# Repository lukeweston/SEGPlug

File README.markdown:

**SEGPlug: A single-channel, single-phase, portable, wireless mesh-networked smart energy data acquisition and control appliance**

Design by Luke Weston, 2011-2012
(c) Luke Weston 2011-2012

This hardware design is released to you under the CERN Open Hardware License: http://ohwr.org/cernohl

The Smart Energy Groups SEGPlug is a small, visually unintrusive and portable device which plugs in to a domestic mains power outlet or cable and plugs into a mains-powered
load device. It is (with a small hardware reconfiguration) compatible with worldwide mains power grids, at 110-240VAC and 50-60 Hz. This "Internet of Things" device collects
data from its sensors and data acquisition circuits and transmits this data to a distributed network and ultimately to the Internet and receives commands from a distributed
network and/or the Internet and responds to such commands, for example by switching its onboard power relay on or off. 

SEGPlug acquires the voltage waveform across the load device(s) and the current waveform being consumed by the load device(s) and calculates instantaneous power draw as well
as energy consumption integrated across some period of time, and complex AC power characteristics such as phase angle, reactive power and power factor.

SEGPlug also incorporates a relay allowing the power supply to the load device to be completely switched off and switched on at the command of the device's (very low power)
internal microcontroller.

SEGPlug is powered from the mains power supply which it is plugged into - no additional power supplies or cables are required, everything is integrated into one clean and
simple plug-in cable.

SEGPlug sends and receives data and commands over a wireless radio mesh network, back to a gateway device which bridges the wireless mesh network onto an existing local area
network which is connected to the Internet - over ethernet, and/or standard IEEE 802.11 wireless networking (Wi-Fi), or 3G or similar cellular networks.

To ensure flexible compatibility with worldwide radiofrequency spectrum licensing and regulations and the device's local electromagnetic environment (with respect to spectrum
congestion, interference, or electromagnetic shielding, reflection or attenuation by nearby structures materials in the environment) SEGPlug's radio communications are handled
on a replaceable daughterboard which can be replaced and swapped with different boards or modules employing different communications frequencies or protocols.

My in-house daughterboard design based around the Atmel ATmega128RFA1 radio/microcontroller can be used, thus providing connectivity over IPv6 / 6LoWPAN etc, as well as
ZigBee. Alternatively, a commercial off-the-shelf product such as a Digi/MaxStream XBee module can be used, operating in the 2.4 GHz or 900 MHz spectra with the ZigBee or
DigiMesh protocols (which are, at their lower layers, also built on the 802.15.4 standard.) A daughterboard based around a sub-gigahertz radio device such as the Texas
Instruments CC1101 IC, operating in the 315/433/868/915 MHz bands can also be used, either in the form of a bespoke RF transceiver from us or a COTS device such as the
Seeed RFBee module.

SEGPlug also incorporates a temperature sensor, for measurement of the temperature in the local environment, a light sensor for sensing of the ambient light level, and support
for an optional PIR motion sensor for the detection of motion and an automated response - for example, turning on the room lights and/or reporting a message to the network.

*Engineering notes for hardware developers, prototype testers, and early adopters:*

This device uses a non-isolated, transformerless mains power supply, with the mains active serving as the local DC ground. What this means is that all parts of the device,
including the microcontroller, XBee module, temperature sensor, and the light and PIR sensors if they're connected, are at mains potential when the device is plugged into the
mains, and all components represent an electric shock hazard. Do not not poke around with this device while it is powered up, with the device not within an earthed enclosure,
or a double-insulated plastic enclosure, unless you know exactly what you're doing.

Also, DO NOT plug the device into any kind of FTDI cable, ISP programmer or any other serial communications interface or programming interface while it is plugged into the
mains. If you do, this will connect your computer's local DC ground to the 240VAC active, and your computer will be destroyed and will probably explode or something, as well
as presenting an electric shock hazard. So don't do it.

It's OK to plug those kinds of interfaces in for programming, obviously, just make damned sure that the mains is unplugged first.

There's nothing "wrong" with a transformerless power supply, though, as long as you understand what it is and what its characteristics are. You'll find very much the same kind
of circuit inside a commercial "kill-a-watt" device, or any similar product. As long as the device does not need to have any cables for data communications out to a computer
or another device, it works absolutely fine. In fact, using this kind of circuit is the only way you're going to keep the size, weight and cost of the device down so that it
is competitive with those kinds of similar commercial products.

The transformerless power supply uses a relatively large cap (2.2 uF) because it needs to supply a relatively large amount of current (about 80 mA) at peak times in order to
reliably run the XBee module (which draws about 50 mA by itself) as well as the relay and AVR without rebooting or crashing the AVR whenever there is a momentary spike in
current draw, whenever the XBee starts transmitting or something like that.

High current means low capacitive reactance which means relatively big capacitor.

Commercial RF modules with relatively high power consumption, such as the Digi/Maxstream "XBee Pro" are unsupported with this system due to power supply constraints in this
design variant and probably won't work reliably, although the standard, lower-power Digi/MaxStream XBee modules are supported. Basically, when using commercial third-party
RF communications modules, the maximum device current consumption during transmission should not exceed 50 mA at 3.3 volts.

It would straightforward to design a safe, optically-isolated plug-in serial cable interface for your computer if something like that was required... but at this point in
time, no such device exists and plugging the unit into your computer (unless the mains is disconnected) is a big no-no.

The maximum power rating of the unit is 10 A at 240 VAC. Do not exceed this limit.

This device is designed for use with 240 VAC mains only. Do not use in a country with a 120 VAC mains supply. It should be possible to change the value of the
capacitive reactance in the mains neutral so that it is OK with 120 VAC operation (which probably means changing the 2.2 uF capacitor to about double its capacitance), but at
the present time this has not been tested and is not supported at all.

The control pushbutton must be rated for mains use. If there is not sufficient electrical isolation between the switch contacts and the plastic switch actuator, an electric
shock hazard may exist during use of the button.

In order to prevent electric shock, fire, explosion, death, etc, careful quality control is required if you're assembling this unit from a kit yourself. Solder everything
carefully, and check that you've got the components oriented correctly with the right kinds of components in the right places.

The 470 uF electrolytic capacitor must be installed with the correct polarity, and the AVR microcontroller must be soldered in with the right orientation.
The 5 different diodes in the circuit all must be installed with the correct polarity and with the right type of diode used in the right spot on the PCB.

**Microcontroller notes, and wireless programming**:

The AVR (which is essentially an Arduino, if it is programmed with an Arduino bootloader) can be reprogrammed remotely via the XBee, if it is programmed with the Arduino
bootloader. Follow the directions here:

http://www.ladyada.net/make/xbee/arduino.html

Note that the hardware configuration at the remote end is already implemented on the board... the XBee modules just need to be configured appropriately and the XBee module
at the host end appropriately connected to a UART interface to the PC.

Note that the AVR is clocked from an 8 MHz crystal and it is running at 3.3V. Therefore, the Arduino IDE must be told that the target device is a 3.3V 8 MHz Arduino prior to
programming.

It is perfectly fine to perform XBee wireless communications and XBee program downloads while the device is plugged into the mains power supply, of course.

During "wired" flashing or programming (either with the ISP programmer or with a FTDI serial cable), the *XBee module must be removed from its socket*.

**Temperature sensor**:

A substantially cheaper Microchip MCP9701 temperature sensor IC with a linear analog output is used to replace the relatively expensive DS18B20 temperature sensor.

**Measurement resolution**:

The power measurement resolution or "granularity" should be about 2.5W per LSB, when operating from 230VAC.

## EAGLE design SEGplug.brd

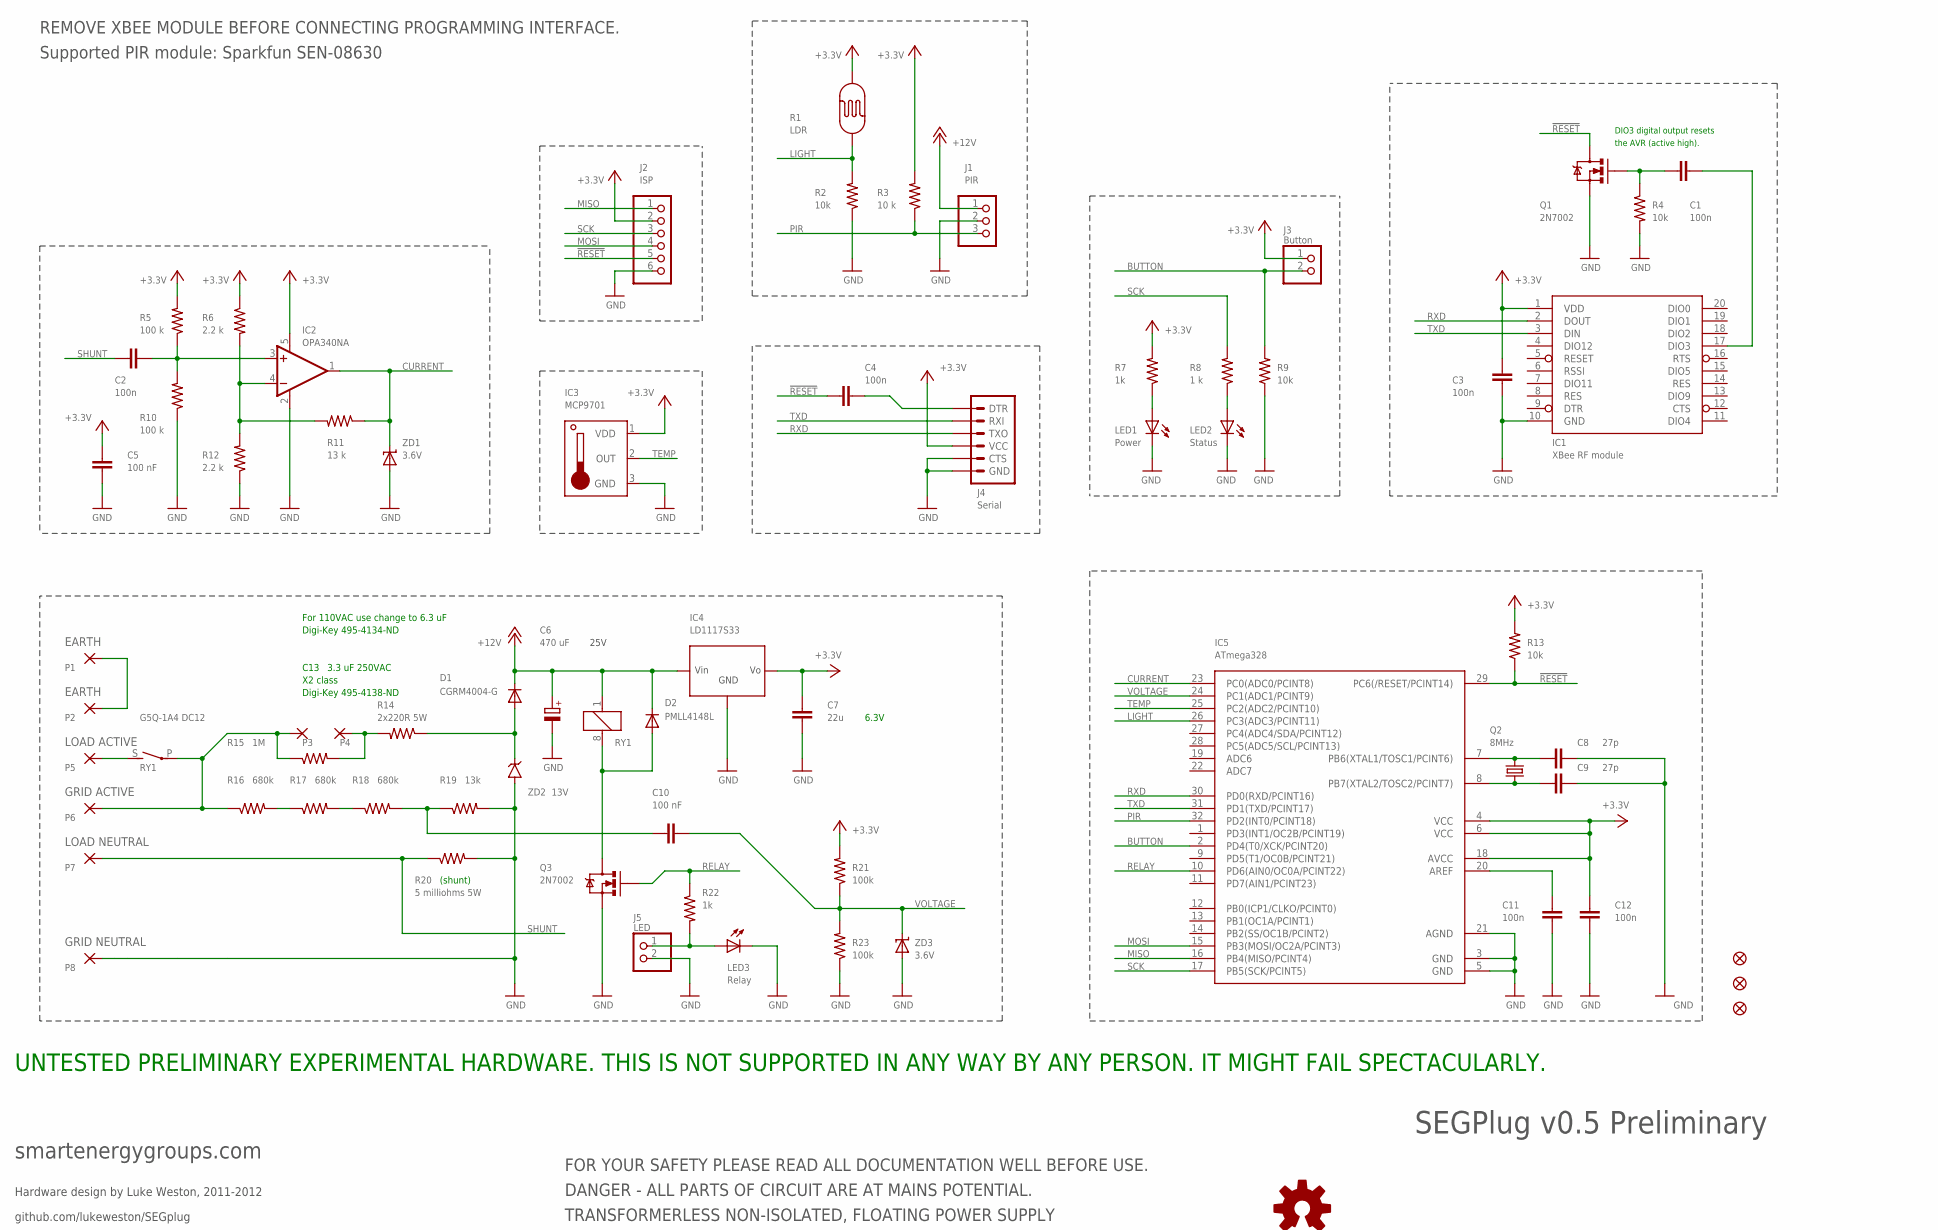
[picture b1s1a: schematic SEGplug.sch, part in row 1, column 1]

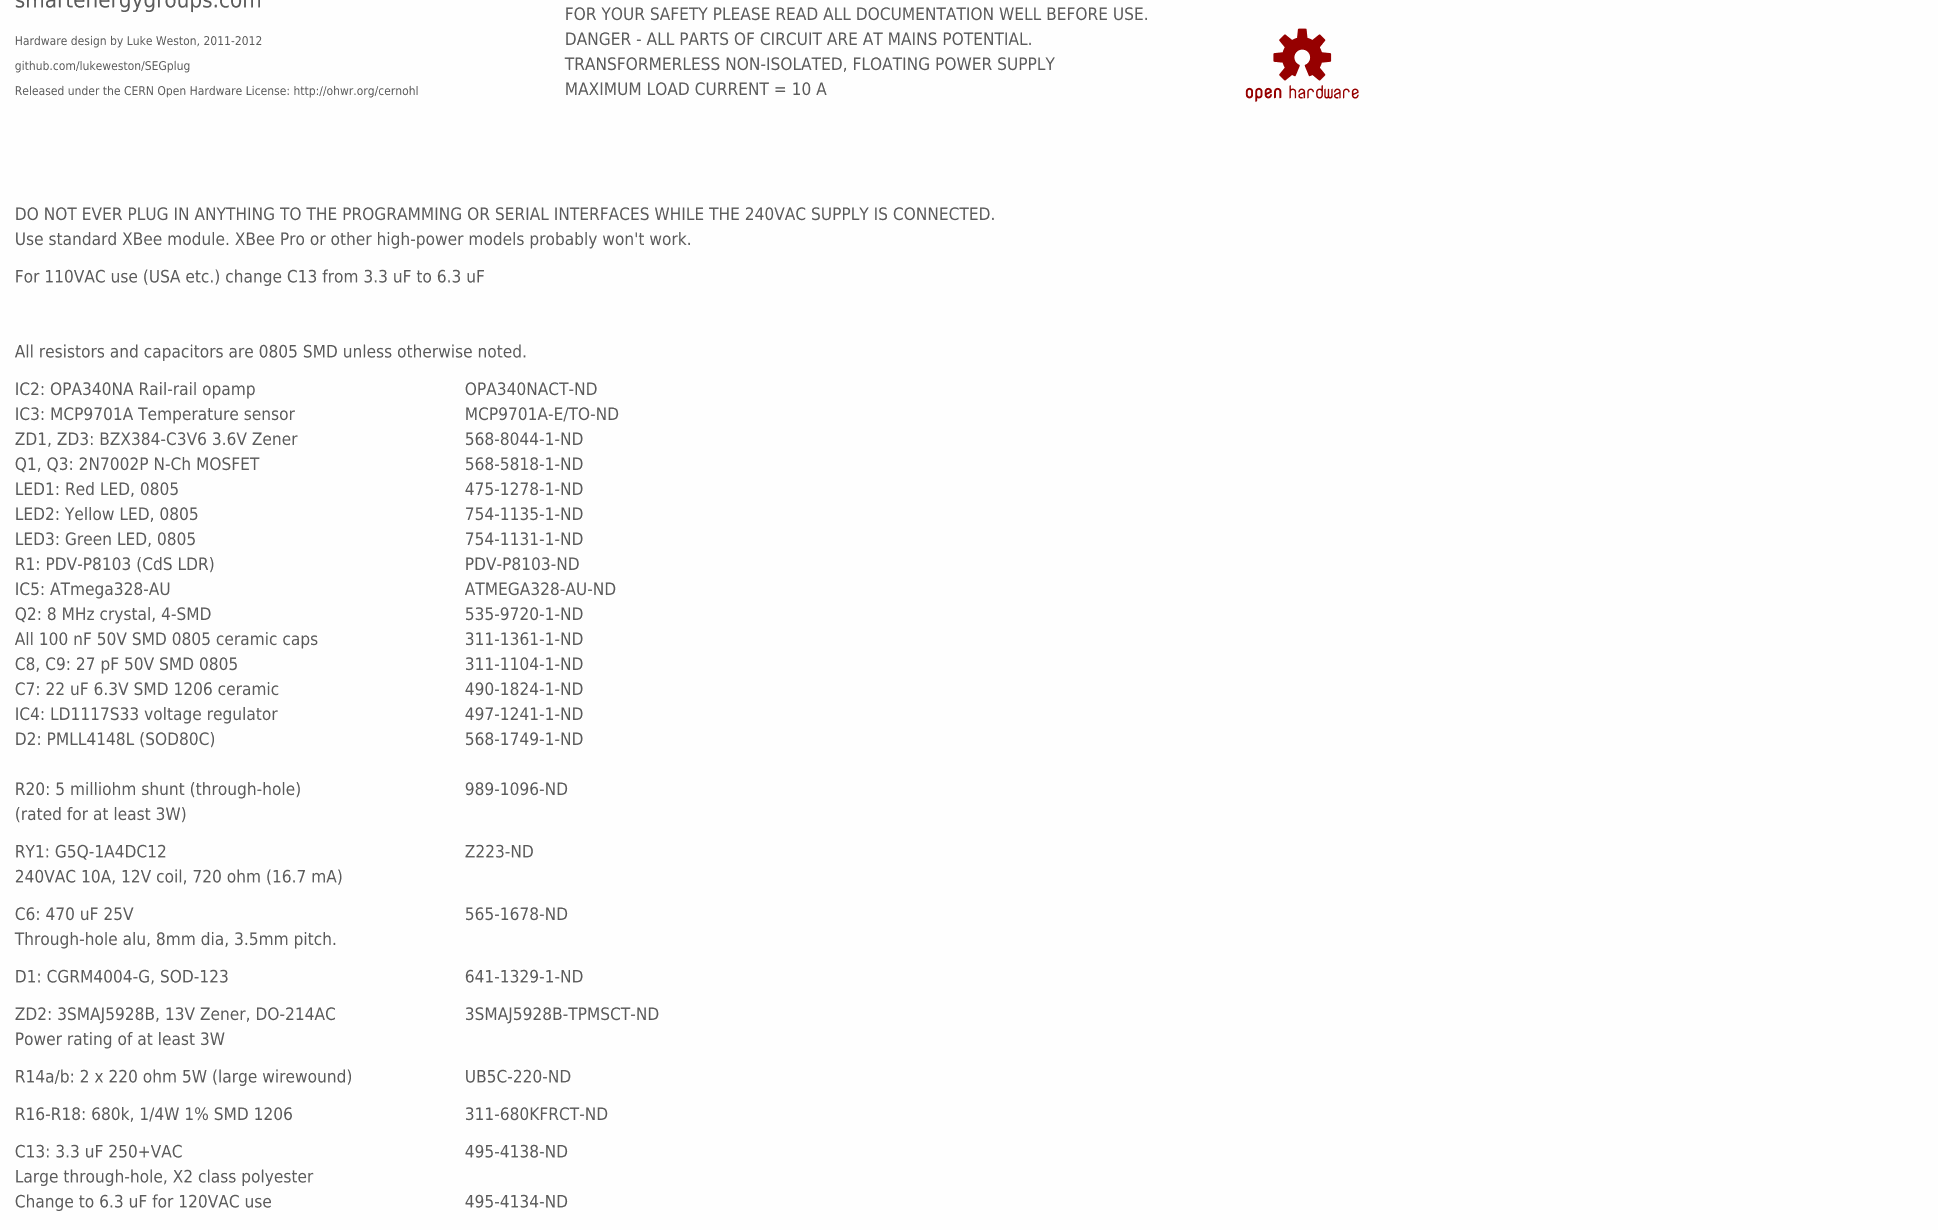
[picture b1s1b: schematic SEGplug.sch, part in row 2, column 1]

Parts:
C1, C2, C3, C4, C11, C12: 100n; C0805K
C5, C10: 100 nF; C0805K
C6: 470 uF; E3,5-8
C7: 22u; C1206K
C8, C9: 27p; C0805K
D1: CGRM4004-G; SOD-123_MINI-SMA
D2: PMLL4148L; MINIMELF
IC1: XBee RF module; XBEE-SMD
IC2: OPA340NA; SOT23-5
IC3: MCP9701; TO92
IC4: LD1117S33; SOT223
IC5: ATmega328; TQFP32-08
J1: PIR; 1X03
J2: ISP; 1X06
J3: Button; 1X02
J4: Serial; 1X06
J5: LED; 1X02
JP1, JP2, JP3: FIDUCIAL1X2; FIDUCIAL-1X2
LED1: Power; CHIPLED_0805
LED2: Status; CHIPLED_0805
LED3: Relay; CHIPLED_0805
P1, P2: EARTH; 4,16O1,6
P3, P4: CAP; 4,16O1,6
P5: LOAD ACTIVE; 4,16O1,6
P6: GRID ACTIVE; 4,16O1,6
P7: LOAD NEUTRAL; 4,16O1,6
P8: GRID NEUTRAL; 4,16O1,6
Q1, Q3: 2N7002; SOT23-3
Q2: 8MHz; CRYSTAL-SMD-5X3
R1: LDR; PHOTOCELL
R2, R4, R9, R13: 10k; M0805
R3: 10 k; M0805
R5, R10: 100 k; M0805
R6, R12: 2.2 k; M0805
R7, R22: 1k; M0805
R8: 1 k; M0805
R11: 13 k; M0805
R14: 2x220R 5W; 0617/17
R15: 1M; M0805
R16, R17, R18: 680k; M1206
R19: 13k; M0805
R20: 5 milliohms 5W; RSENSE2_RSENSE
R21, R23: 100k; M0805
RY1: G5Q-1A4 DC12; G6C-1117P
U$: OSHW-LOGOS; OSHW-LOGO-S
ZD1, ZD3: 3.6V; SOD-323
ZD2: 13V; DO214AC

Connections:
!RESET: C4.2, IC5.29 (PC6(/RESET/PCINT14)), J2.5, Q1.3 (D), R13.1
+3V3: C3.1, C5.1, C7.1, C12.1, IC1.1 (VDD), IC2.5 (V+), IC3.1 (VDD), IC4.2 (VOUT), IC5.4 (VCC), IC5.6 (VCC), IC5.18 (AVCC), J2.2, J3.1, J4.4 (VCC), R1.2, R3.2, R5.2, R6.1, R7.2, R13.2, R21.2
+12V: C6.+, D1.C, D2.C, IC4.3 (VIN), J1.1, RY1.1
BUTTON: IC5.2 (PD4(T0/XCK/PCINT20)), J3.2, R9.2
CURRENT: IC2.1 (OUT), IC5.23 (PC0(ADC0/PCINT8)), R11.1, ZD1.1 (C)
DIO3: C1.1, IC1.17 (DIO3)
GND: C3.2, C5.2, C6.-, C7.2, C8.2, C9.2, C11.2, C12.2, IC1.10 (GND), IC2.2 (V-), IC3.3 (GND), IC4.1 (GND), IC5.3 (GND), IC5.5 (GND), IC5.21 (AGND), J1.2, J2.6, J4.5 (CTS), J4.6 (GND), J5.2, LED1.C, LED2.C, LED3.C, P8.1, Q1.2 (S), Q3.2 (S), R2.1, R4.2, R9.1, R10.1, R12.1, R19.2, R20.P$2 (2), R23.1, ZD1.2 (A), ZD2.A, ZD3.2 (A)
LIGHT: IC5.26 (PC3(ADC3/PCINT11)), R1.1, R2.2
MISO: IC5.16 (PB4(MISO/PCINT4)), J2.1
MOSI: IC5.15 (PB3(MOSI/OC2A/PCINT3)), J2.4
unnamed: LED1.A, R7.1
unnamed: P3.1, P6.1, R15.1, R16.1, RY1.P
unnamed: R17.2, R18.1
unnamed: D2.A, Q3.3 (D), RY1.8 (2)
unnamed: J5.1, LED3.A, R22.2
unnamed: P5.1, RY1.S
unnamed: C11.1, IC5.20 (AREF)
unnamed: P1.1, P2.1
unnamed: C8.1, IC5.7 (PB6(XTAL1/TOSC1/PCINT6)), Q2.3 (2)
unnamed: C9.1, IC5.8 (PB7(XTAL2/TOSC2/PCINT7)), Q2.1
unnamed: LED2.A, R8.1
unnamed: C1.2, Q1.1 (G), R4.1
unnamed: P4.1, R14.2, R15.2
unnamed: D1.A, R14.1, ZD2.C
unnamed: C10.2, R18.2, R19.1
unnamed: C4.1, J4.1 (DTR)
unnamed: R16.2, R17.1
unnamed: IC2.4 (-IN), R6.2, R11.2, R12.2
unnamed: C2.1, IC2.3 (+IN), R5.1, R10.2
PIR: IC5.32 (PD2(INT0/PCINT18)), J1.3, R3.1
RELAY: IC5.10 (PD6(AIN0/OC0A/PCINT22)), Q3.1 (G), R22.1
RXD: IC1.2 (DOUT), IC5.30 (PD0(RXD/PCINT16)), J4.3 (TXO)
SCK: IC5.17 (PB5(SCK/PCINT5)), J2.3, R8.2
SHUNT: C2.2, P7.1, R20.P$1 (1)
TEMP: IC3.2 (OUT), IC5.25 (PC2(ADC2/PCINT10))
TXD: IC1.3 (DIN), IC5.31 (PD1(TXD/PCINT17)), J4.2 (RXI)
VOLTAGE: C10.1, IC5.24 (PC1(ADC1/PCINT9)), R21.1, R23.2, ZD3.1 (C)

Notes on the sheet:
DANGER - ALL PARTS OF CIRCUIT ARE AT MAINS POTENTIAL.
DO NOT EVER PLUG IN ANYTHING TO THE PROGRAMMING OR SERIAL INTERFACES WHILE THE 240VAC SUPPLY IS CONNECTED.
MAXIMUM LOAD CURRENT = 10 A
REMOVE XBEE MODULE BEFORE CONNECTING PROGRAMMING INTERFACE.
Hardware design by Luke Weston, 2011-2012
Released under the CERN Open Hardware License: http://ohwr.org/cernohl
Use standard XBee module. XBee Pro or other high-power models probably won't work.
DIO3 digital output resets
SEGPlug v0.5 Preliminary
smartenergygroups.com
UNTESTED PRELIMINARY EXPERIMENTAL HARDWARE. THIS IS NOT SUPPORTED IN ANY WAY BY ANY PERSON. IT MIGHT FAIL SPECTACULARLY.
github.com/lukeweston/SEGplug
6.3V
For 110VAC use (USA etc.) change C13 from 3.3 uF to 6.3 uF
240VAC 10A, 12V coil, 720 ohm (16.7 mA)
TRANSFORMERLESS NON-ISOLATED, FLOATING POWER SUPPLY
Supported PIR module: Sparkfun SEN-08630
FOR YOUR SAFETY PLEASE READ ALL DOCUMENTATION WELL BEFORE USE.
25V
3.3 uF 250VAC
X2 class
(shunt)
C13
the AVR (active high).
All resistors and capacitors are 0805 SMD unless otherwise noted.
IC2: OPA340NA Rail-rail opamp
ZD1, ZD3: BZX384-C3V6 3.6V Zener
IC3: MCP9701A Temperature sensor
R1: PDV-P8103 (CdS LDR)
Q1, Q3: 2N7002P N-Ch MOSFET
LED3: Green LED, 0805
LED1: Red LED, 0805
LED2: Yellow LED, 0805
OPA340NACT-ND
MCP9701A-E/TO-ND
568-8044-1-ND
568-5818-1-ND
475-1278-1-ND
754-1135-1-ND
754-1131-1-ND

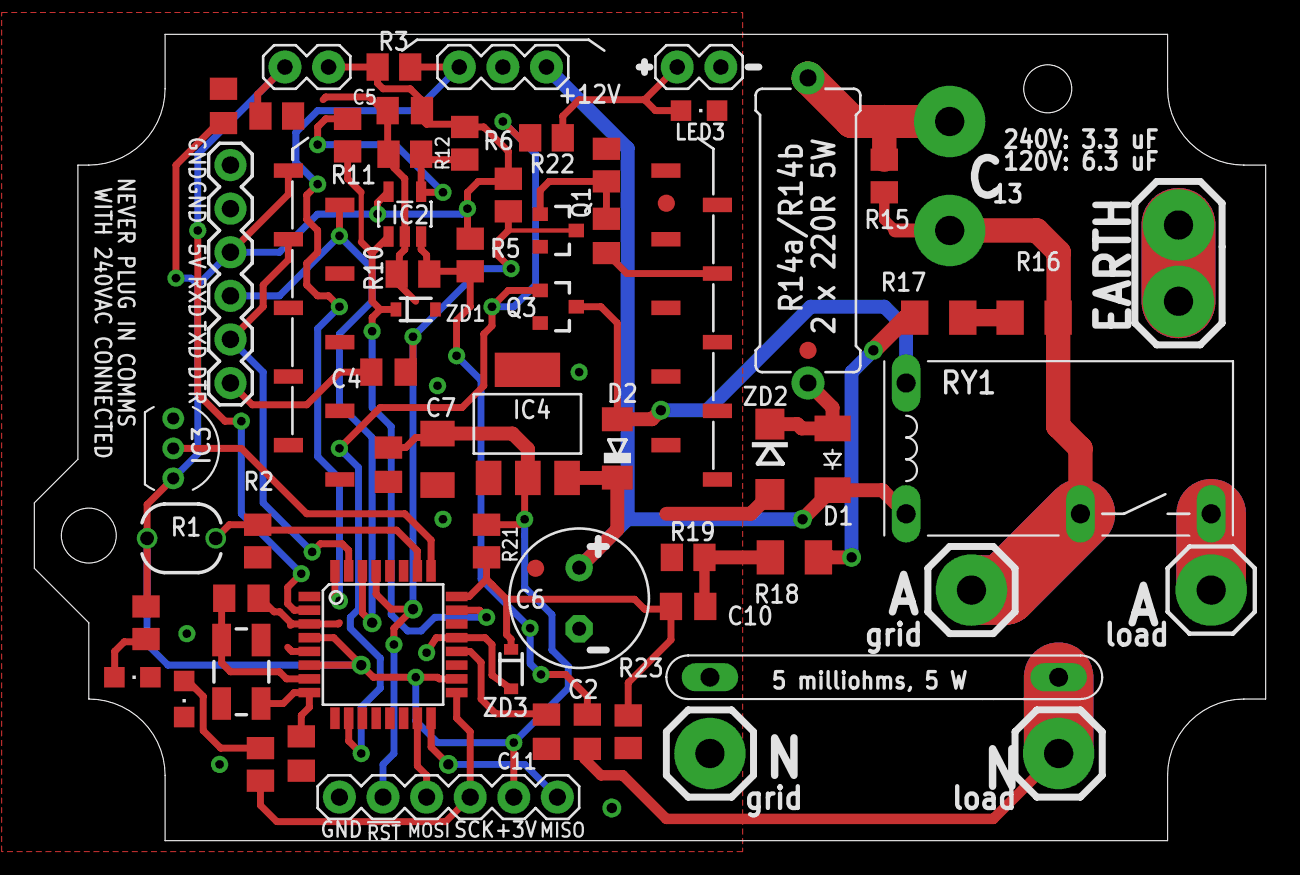
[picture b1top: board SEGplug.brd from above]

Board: 2 copper layers, 71.8 x 47.0 mm, 69 parts (1 on the bottom side), 37 nets.

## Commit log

2012-02-09 partially completed new revised design
2012-03-07 Finished new design
2012-03-07 edited readme
